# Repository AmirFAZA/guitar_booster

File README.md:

```markdown

```
```markdown

```
```markdown

```

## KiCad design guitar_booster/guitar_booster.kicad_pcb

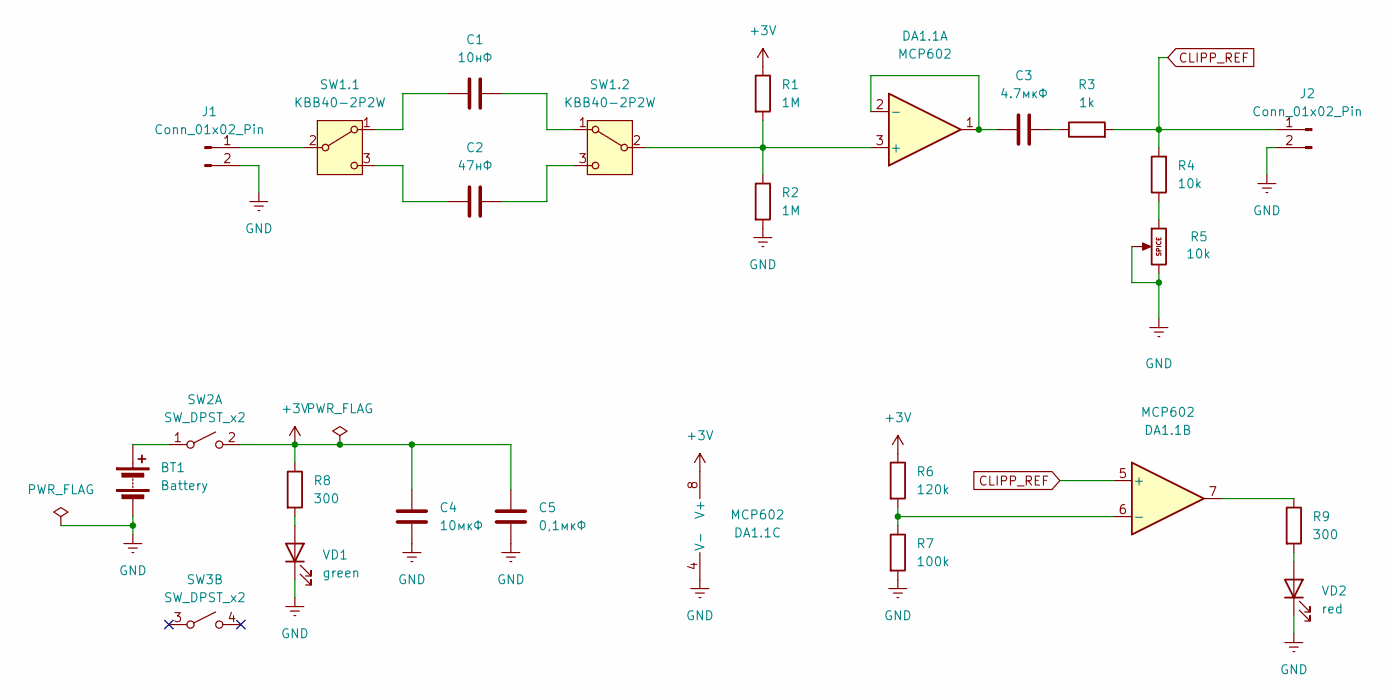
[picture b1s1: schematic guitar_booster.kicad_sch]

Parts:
BT1: Battery; MagneticBuzzer_Kingstate_KCG0601
C1: 10нФ; C_0603_1608Metric
C2: 47нФ; C_0603_1608Metric
C3: 4.7мкФ; C_0603_1608Metric
C4: 10мкФ; C_0603_1608Metric
C5: 0,1мкФ; C_0603_1608Metric
DA1.1: MCP602; SOIC-8_3.9x4.9mm_P1.27mm
J1, J2: Conn_01x02_Pin; PinHeader_1x02_P2.54mm_Vertical
R1, R2: 1M; R_0603_1608Metric
R3: 1k; R_0603_1608Metric
R4: 10k; R_0603_1608Metric
R5: 10k; PinHeader_1x03_P2.54mm_Vertical
R6: 120k; R_0603_1608Metric
R7: 100k; R_0603_1608Metric
R8, R9: 300; R_0603_1608Metric
SW1.1, SW1.2: KBB40-2P2W; PinHeader_1x03_P2.54mm_Vertical
SW2: SW_DPST_x2; PinHeader_1x02_P2.54mm_Vertical
SW3: SW_DPST_x2
VD1: green; LED_D1.8mm_W3.3mm_H2.4mm
VD2: red; LED_D1.8mm_W3.3mm_H2.4mm

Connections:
+3V: C4.2, C5.2, DA1.1.8 (V+), R1.1, R6.1, R8.1, SW2.2 (B)
CLIPP_REF: DA1.1.5 (+), J2.1, R3.2, R4.2
GND: BT1.2 (-), C4.1, C5.1, DA1.1.4 (V-), J1.2, J2.2, R2.2, R5.2, R5.3, R7.2, VD1.1 (K), VD2.1 (K)
unnamed: BT1.1 (+), SW2.1 (A)
unnamed: C3.2, R3.1
unnamed: DA1.1.7, R9.1
unnamed: DA1.1.3 (+), R1.2, R2.1, SW1.2.2 (B)
unnamed: C3.1, DA1.1.1, DA1.1.2 (-)
unnamed: DA1.1.6 (-), R6.2, R7.1
unnamed: J1.1, SW1.1.2 (B)
unnamed: R4.1, R5.1
unnamed: C1.1, SW1.1.1 (A)
unnamed: C2.1, SW1.1.3 (C)
unnamed: C1.2, SW1.2.1 (A)
unnamed: C2.2, SW1.2.3 (C)
unnamed: R8.2, VD1.2 (A)
unnamed: R9.2, VD2.2 (A)

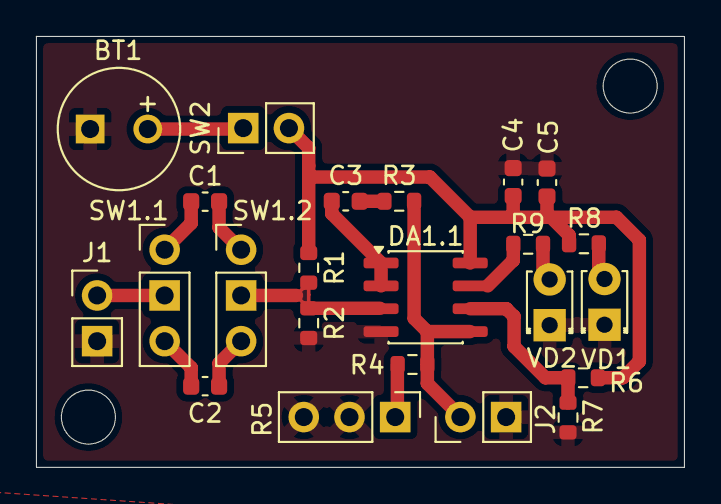
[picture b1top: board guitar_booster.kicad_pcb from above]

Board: 2 copper layers, 36.0 x 23.9 mm, 23 parts (0 on the bottom side), 17 nets.
